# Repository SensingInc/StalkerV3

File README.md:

# StalkerV3
Repository for development of the Stalker stem strength tester.

## Introduction
The Stalker is an instrument for measuring stalk or stem strength in plants. Its development, building, and use is outlined in this HardwareX paper: https://www.sciencedirect.com/science/article/pii/S2468067218301184

and its data analysis (and theory of operation) is outlined in this Applied Sciences paper: https://www.mdpi.com/2076-3417/10/22/7965

The bill of materials can be found here: https://docs.google.com/spreadsheets/d/1YpdJ8Psb1IhpG5ddTsx0BFufkG1ZGOrEwDEdpia4aTM/edit?usp=sharing

## Contents
This repository contains the firmware (Stalkerv3B.ino) and the schematic (MainBoard.sch) and board (MainBoard.brd) files to build and program the internals of the latest version of the Stalker.

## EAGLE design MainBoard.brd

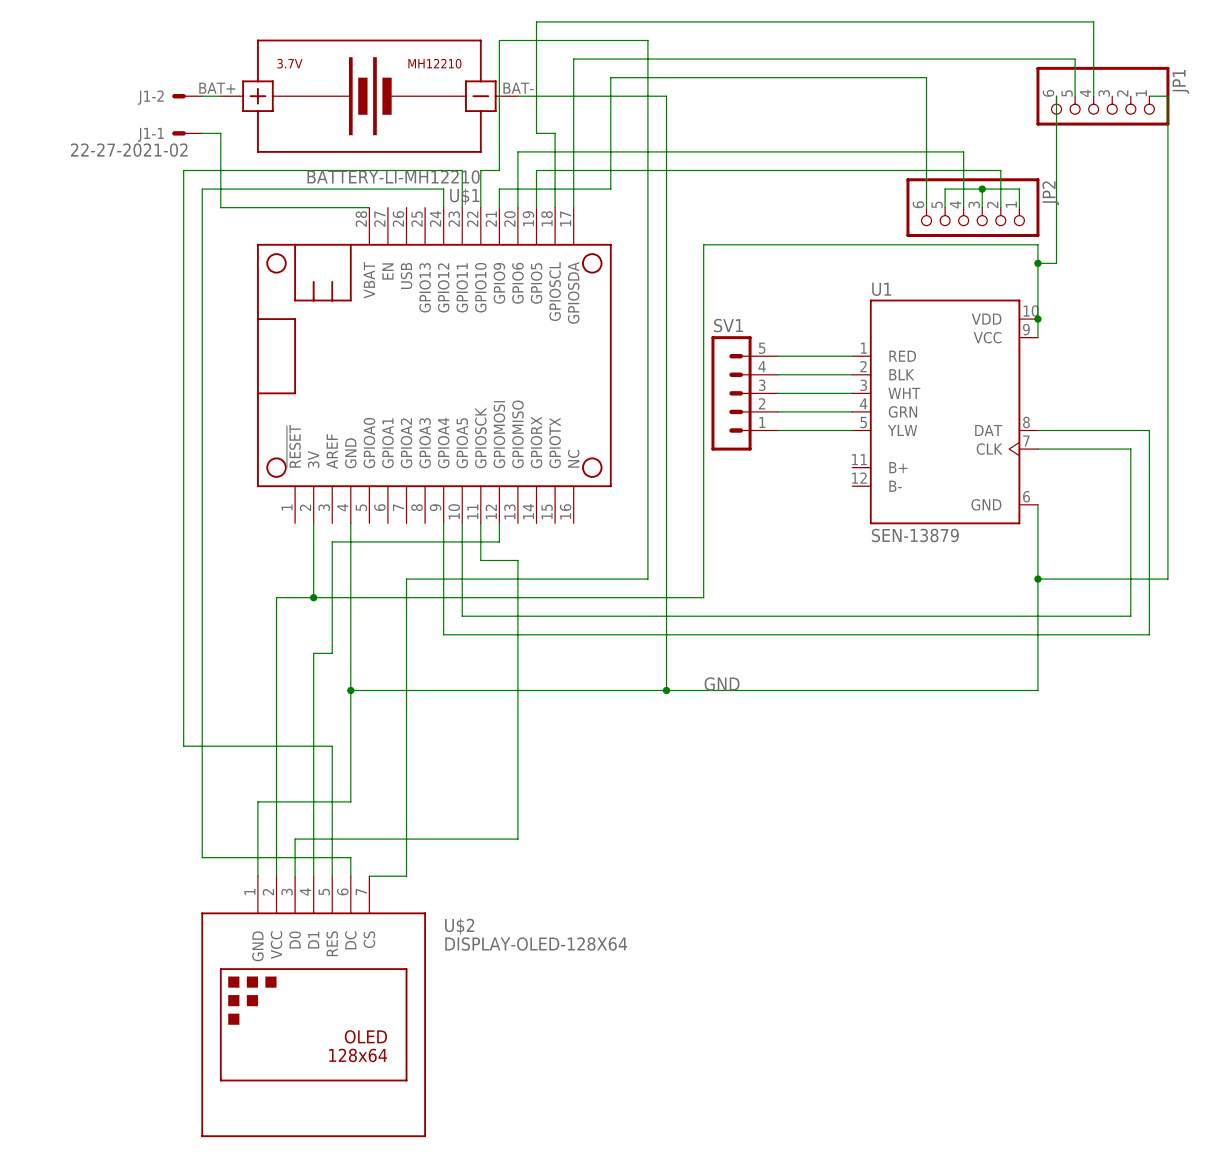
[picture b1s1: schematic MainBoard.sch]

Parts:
J1: 22-27-2021-02; 6410-02
JP1, JP2: PINHD-1X6; 1X06
MS1: FEATHERWING_NODIM; FEATHERWING_DIM
SV1: MA05-1
U1: SEN-13879; SPARKFUN_SEN-13879
U$1: BATTERY-LI-MH12210
U$2: DISPLAY-OLED-128X64

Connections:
3V: JP1.6, MS1.2 (3V), U1.9 (VCC), U1.10 (VDD), U$2.2 (VCC)
GND: JP1.1, MS1.4 (GND), U1.6 (GND), U$1.BAT-, U$2.1 (GND)
unnamed: JP2.2, MS1.19 (GPIO5)
unnamed: MS1.9 (GPIOA4), U1.8 (DAT)
unnamed: MS1.10 (GPIOA5), U1.7 (CLK)
unnamed: J1.2, U$1.BAT+
unnamed: SV1.1, U1.5 (YLW)
unnamed: SV1.2, U1.4 (GRN)
unnamed: SV1.3, U1.3 (WHT)
unnamed: JP2.4, MS1.20 (GPIO6)
unnamed: JP2.6, MS1.21 (GPIO9)
unnamed: MS1.22 (GPIO10), U$2.7 (CS)
unnamed: MS1.11 (GPIOSCK), U$2.3 (D0)
unnamed: MS1.12 (GPIOMOSI), U$2.4 (D1)
unnamed: MS1.23 (GPIO11), U$2.5 (RES)
unnamed: MS1.24 (GPIO12), U$2.6 (DC)
unnamed: SV1.4, U1.2 (BLK)
unnamed: SV1.5, U1.1 (RED)
unnamed: JP1.4, MS1.18 (GPIOSCL)
unnamed: JP2.1, JP2.3, JP2.5
SDA: JP1.5, MS1.17 (GPIOSDA)
VBAT: J1.1, MS1.28 (VBAT)

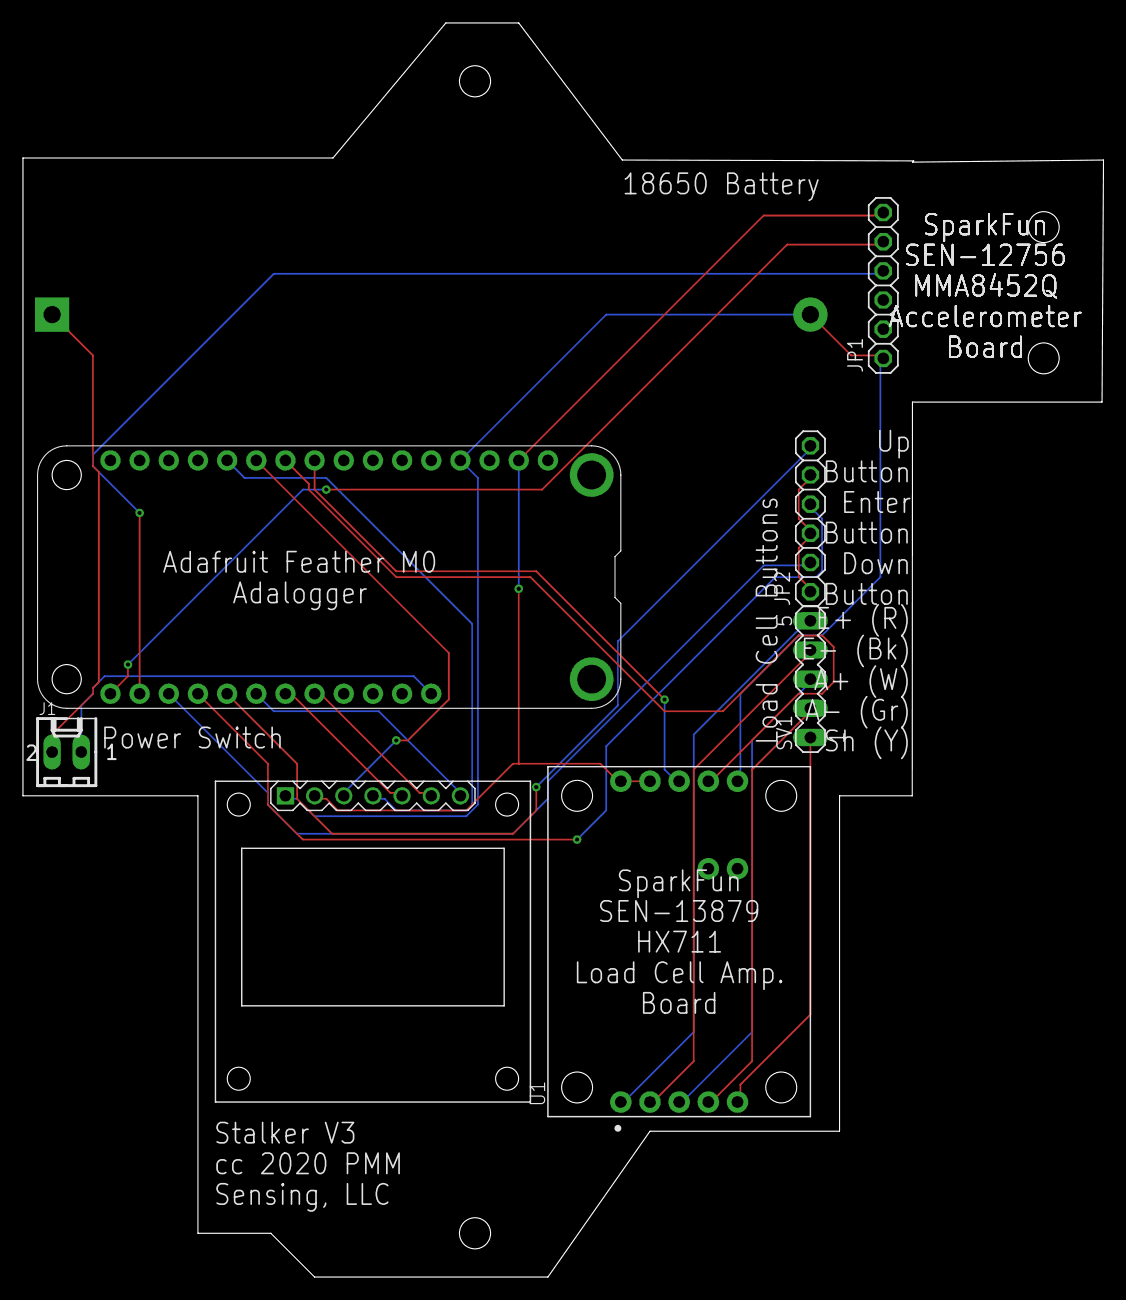
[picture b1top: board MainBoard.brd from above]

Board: 2 copper layers, 94.1 x 109.2 mm, 8 parts (1 on the bottom side), 22 nets.

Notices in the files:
parts and their libraries:
diy-modules: Released under the Creative Commons Attribution 4.0 International License: http://creativecommons.org/licenses/by/4.0
